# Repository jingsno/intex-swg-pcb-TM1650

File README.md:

# Intex SWG automaton

This is a PCB for Intex SWG Automation

Original code/repository made by Tonny Flores at
https://github.com/tonyflores1006/intex-swg-iot

Cleaned up repository at
https://github.com/jressel01/intex-swg-iot

Discussion here
https://www.troublefreepool.com/threads/automation-of-intex-swg.228606/

This PCB is suitable for the TM1650 (16 pin) display board.

For a "non TM1650 version" (18 pin) of the pcb/code see 
https://github.com/jingsno/intex-swg-pcb

*PCB for Intex SWG automation*

## Schematic

Link to [PDF Schematic](docs/intex-swg-pcb.pdf)

## Parts list

| Part            |             |
|-----------------|-------------|
| ESP32-DevkitC ext antenna |  https://www.digikey.com/en/products/detail/espressif-systems/ESP32-DEVKITC-32U/9357002 |
| IRM-03-5 | https://www.digikey.com/en/products/detail/mean-well-usa-inc/IRM-03-5/7704640 |
| Level shifter to/from 5V/3.3V | https://www.aliexpress.com/item/1005001621978054.html | 
| 3.3V Relay module | https://www.aliexpress.com/item/32884967707.html | 
| 2x Female and 1x Male XH2.54 4pin connectors | https://www.aliexpress.com/item/4000126563819.html | 
| Stepper Motor cables/wire XH2.54 4pin | https://www.aliexpress.com/item/1005001361294507.html |
| Fuse 3A / 250V | https://www.aliexpress.com/item/32702176964.html | 
| 2-pin screw terminal | https://www.aliexpress.com/item/1005002971443405.html  | 
| 3-pin screw terminal | https://www.aliexpress.com/item/1005002971443405.html  |

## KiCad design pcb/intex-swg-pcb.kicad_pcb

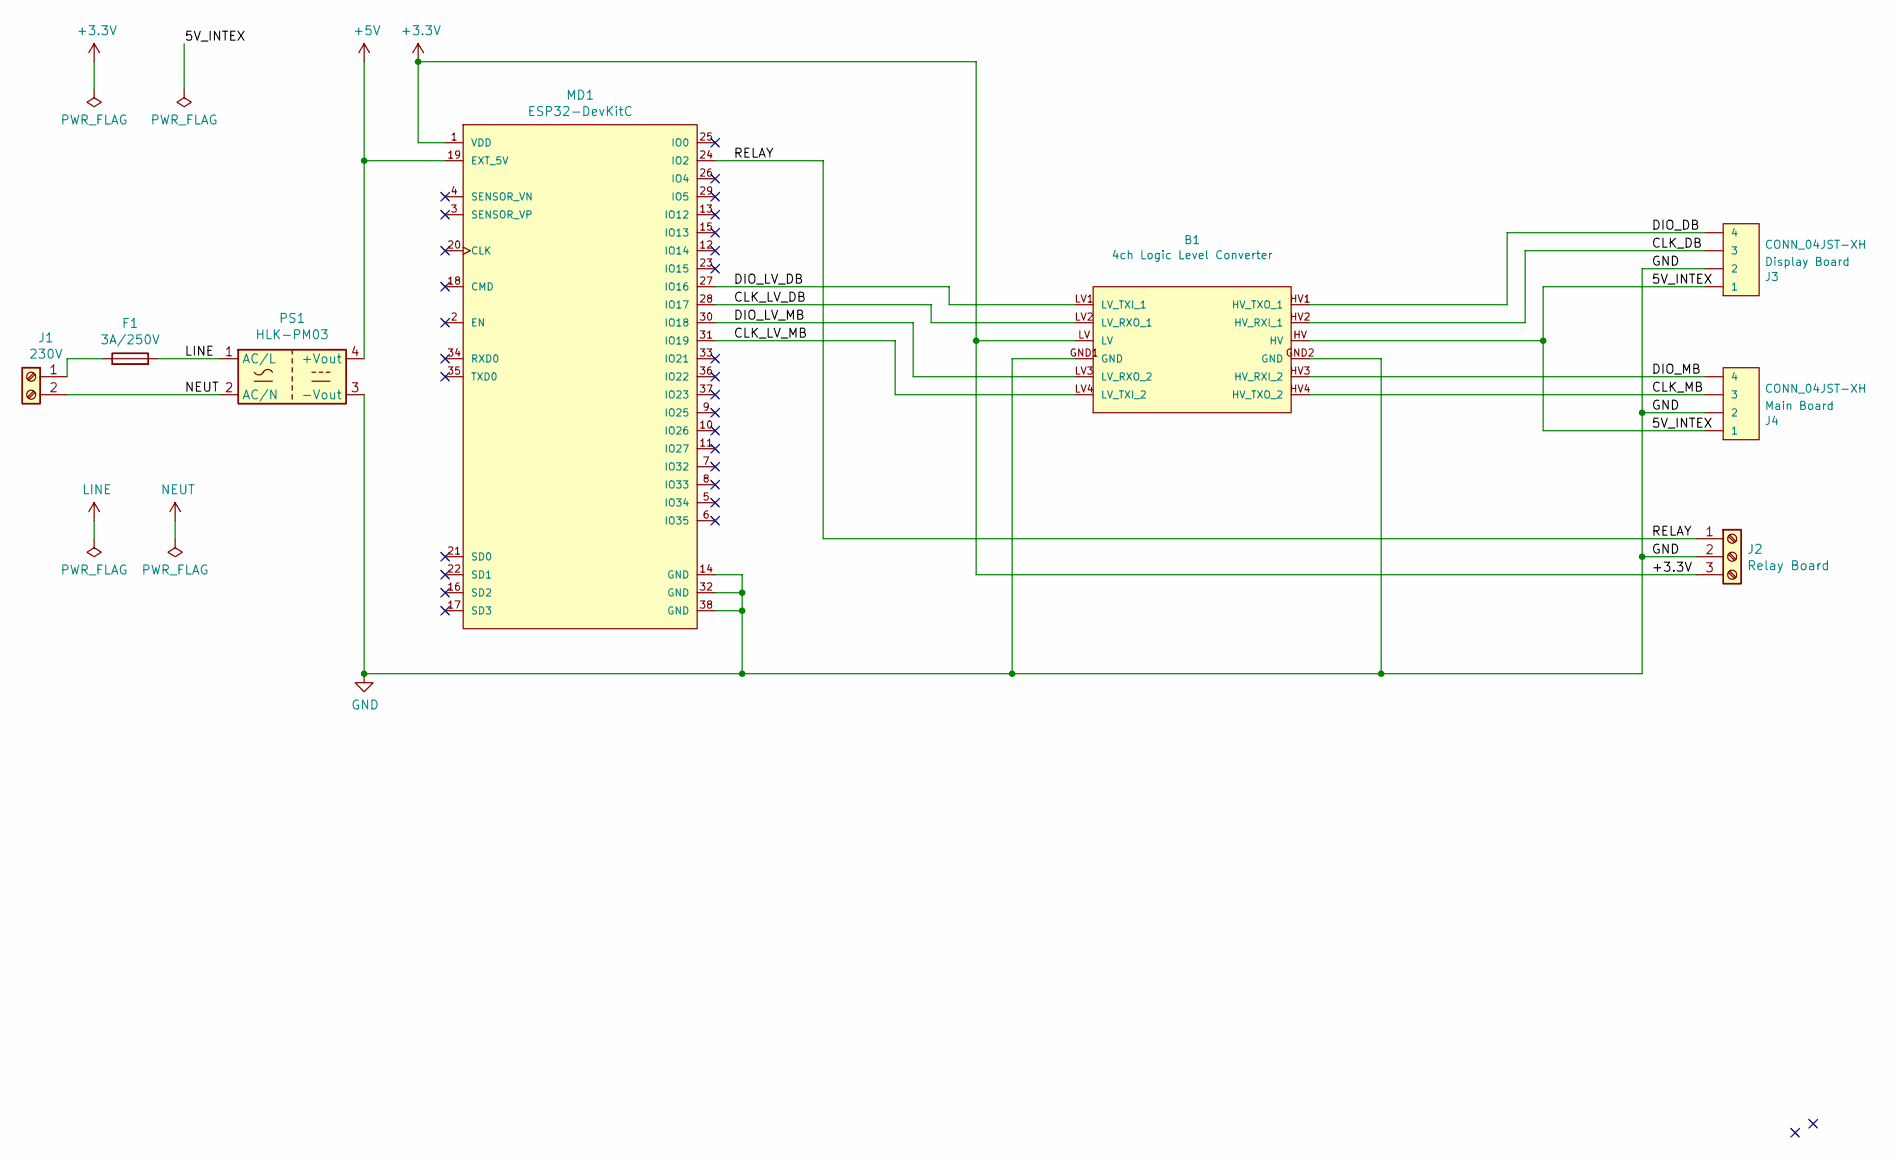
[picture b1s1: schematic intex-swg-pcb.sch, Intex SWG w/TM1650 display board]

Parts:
B1: 4ch Logic Level Converter; SPARKFUN_LOGIC_LEVEL_CONVERTER; digi-key part number 1568-1209-ND
F1: 3A/250V; Fuse_Littelfuse-LVR100
J1: 230V; TerminalBlock_Phoenix_MKDS-1,5-2_1x02_P5.00mm_Horizontal
J2: Relay Board; TerminalBlock_Phoenix_MKDS-1,5-3_1x03_P5.00mm_Horizontal
J3: Display Board; JST_XH_B4B-XH-A_1x04_P2.50mm_Vertical
J4: Main Board; JST_XH_B4B-XH-A_1x04_P2.50mm_Vertical
MD1: ESP32-DevKitC; Espressif-ESP32-DevKitC_V4-0-0-MFG; mouser part number 356-ESP32-DEVKITC
PS1: HLK-PM03; Converter_ACDC_HiLink_HLK-PMxx

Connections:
+3V3: B1.LV, J2.3, MD1.1 (VDD)
+5V: MD1.19 (EXT_5V), PS1.4 (+Vout)
/5V_INTEX: B1.HV, J3.1, J4.1
/CLK_DB: B1.HV2 (HV_RXI_1), J3.3
/CLK_LV_DB: B1.LV2 (LV_RXO_1), MD1.28 (IO17)
/CLK_LV_MB: B1.LV4 (LV_TXI_2), MD1.31 (IO19)
/CLK_MB: B1.HV4 (HV_TXO_2), J4.3
/DIO_DB: B1.HV1 (HV_TXO_1), J3.4
/DIO_LV_DB: B1.LV1 (LV_TXI_1), MD1.27 (IO16)
/DIO_LV_MB: B1.LV3 (LV_RXO_2), MD1.30 (IO18)
/DIO_MB: B1.HV3 (HV_RXI_2), J4.4
/RELAY: J2.1, MD1.24 (IO2)
GND: B1.GND1 (GND), B1.GND2 (GND), J2.2, J3.2, J4.2, MD1.14 (GND), MD1.32 (GND), MD1.38 (GND), PS1.3 (-Vout)
LINE: F1.2, PS1.1 (AC/L)
NEUT: J1.2, PS1.2 (AC/N)
unnamed: F1.1, J1.1

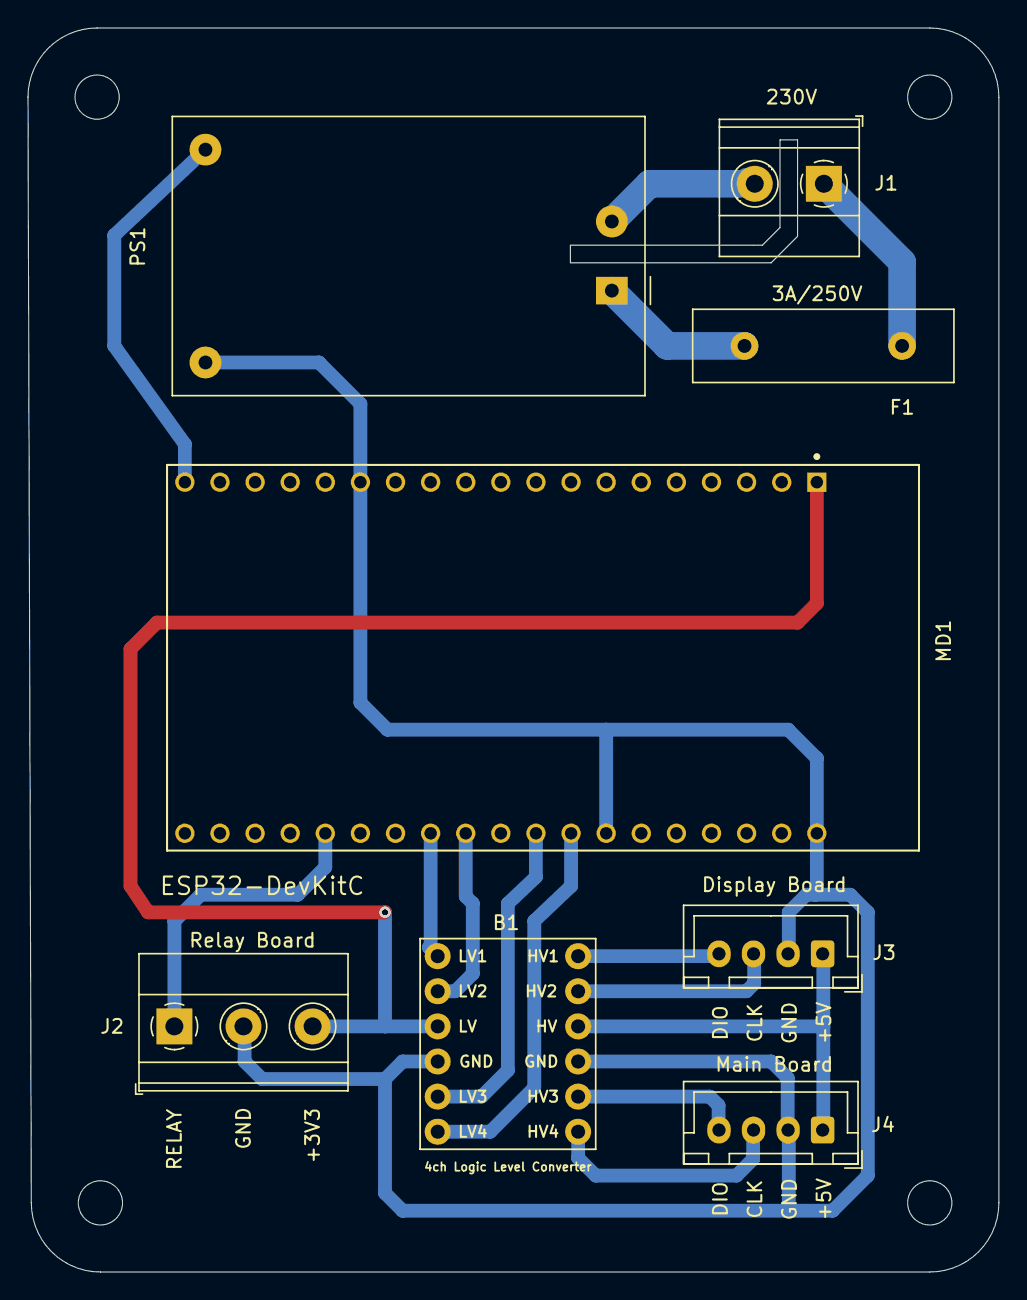
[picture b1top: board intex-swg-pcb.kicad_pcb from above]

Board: 2 copper layers, 70.2 x 90.0 mm, 8 parts (0 on the bottom side), 16 nets.

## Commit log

2022-05-22 Updated .gitignore
2022-05-22 Fixed readme
2022-06-06 Redirect to universal PCB repository
2022-06-06 Redirect to universal PCB
2022-06-11 Swapped relay to GPIO2
2022-06-11 Removed obsolete files
